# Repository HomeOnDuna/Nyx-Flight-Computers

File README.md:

# Nyx-Flight-Computer
Contains all details of the Nyx family of flight computers developed by Timothy Paige for UNSW rocketry

How to use:
 - Make a local clone of the entire repositry
 - Open the project you want from the file it is in
 - Enjoy!

To add parts to the library:
 - All parts go in the UNSW Rocketry parts folder (single parrts library)
 - Open a project and add the symbol into the UNSW Rocketry Library (symbol library, via import)
 - Put the footprint in the footprints.pretty folder of the parts folder
 - Put the 3D model in the 3D models folder
 - In the project, edit the symbol you have imported and assign the default footprint to the footprints.pretty folder footprint (.kicad_mod)
 - Edit the footprint you just added to add in the 3D model

How to reference filepaths:
**Do not use the default filepaths KiCAD generates. These will only work on your device!**
 - Remove the filepath up to Nyx-Flight-Computers (leave the \ after this)
 - Insert .. before this, which then re-references to a relative filepath (permitting multi-device use).

Current capabilites:
 - Literally nothing

Future capabilities targets:
 - Flight data recording from multiple sources to memory (SD cards)
 - Detection of phase of flight (not vehicle direction, speed etc., only are we 1) accelerating, and 2) going up or going down) and subsequent actions or data recording changes
 - Flight data high-speed capability to RAM during boost phase
 - Telemetry of currently relevant data
 - Pyro / chute deploy devices (linear actuator or other form)
 - Basic marking out of failed / erroring sensors in data recording

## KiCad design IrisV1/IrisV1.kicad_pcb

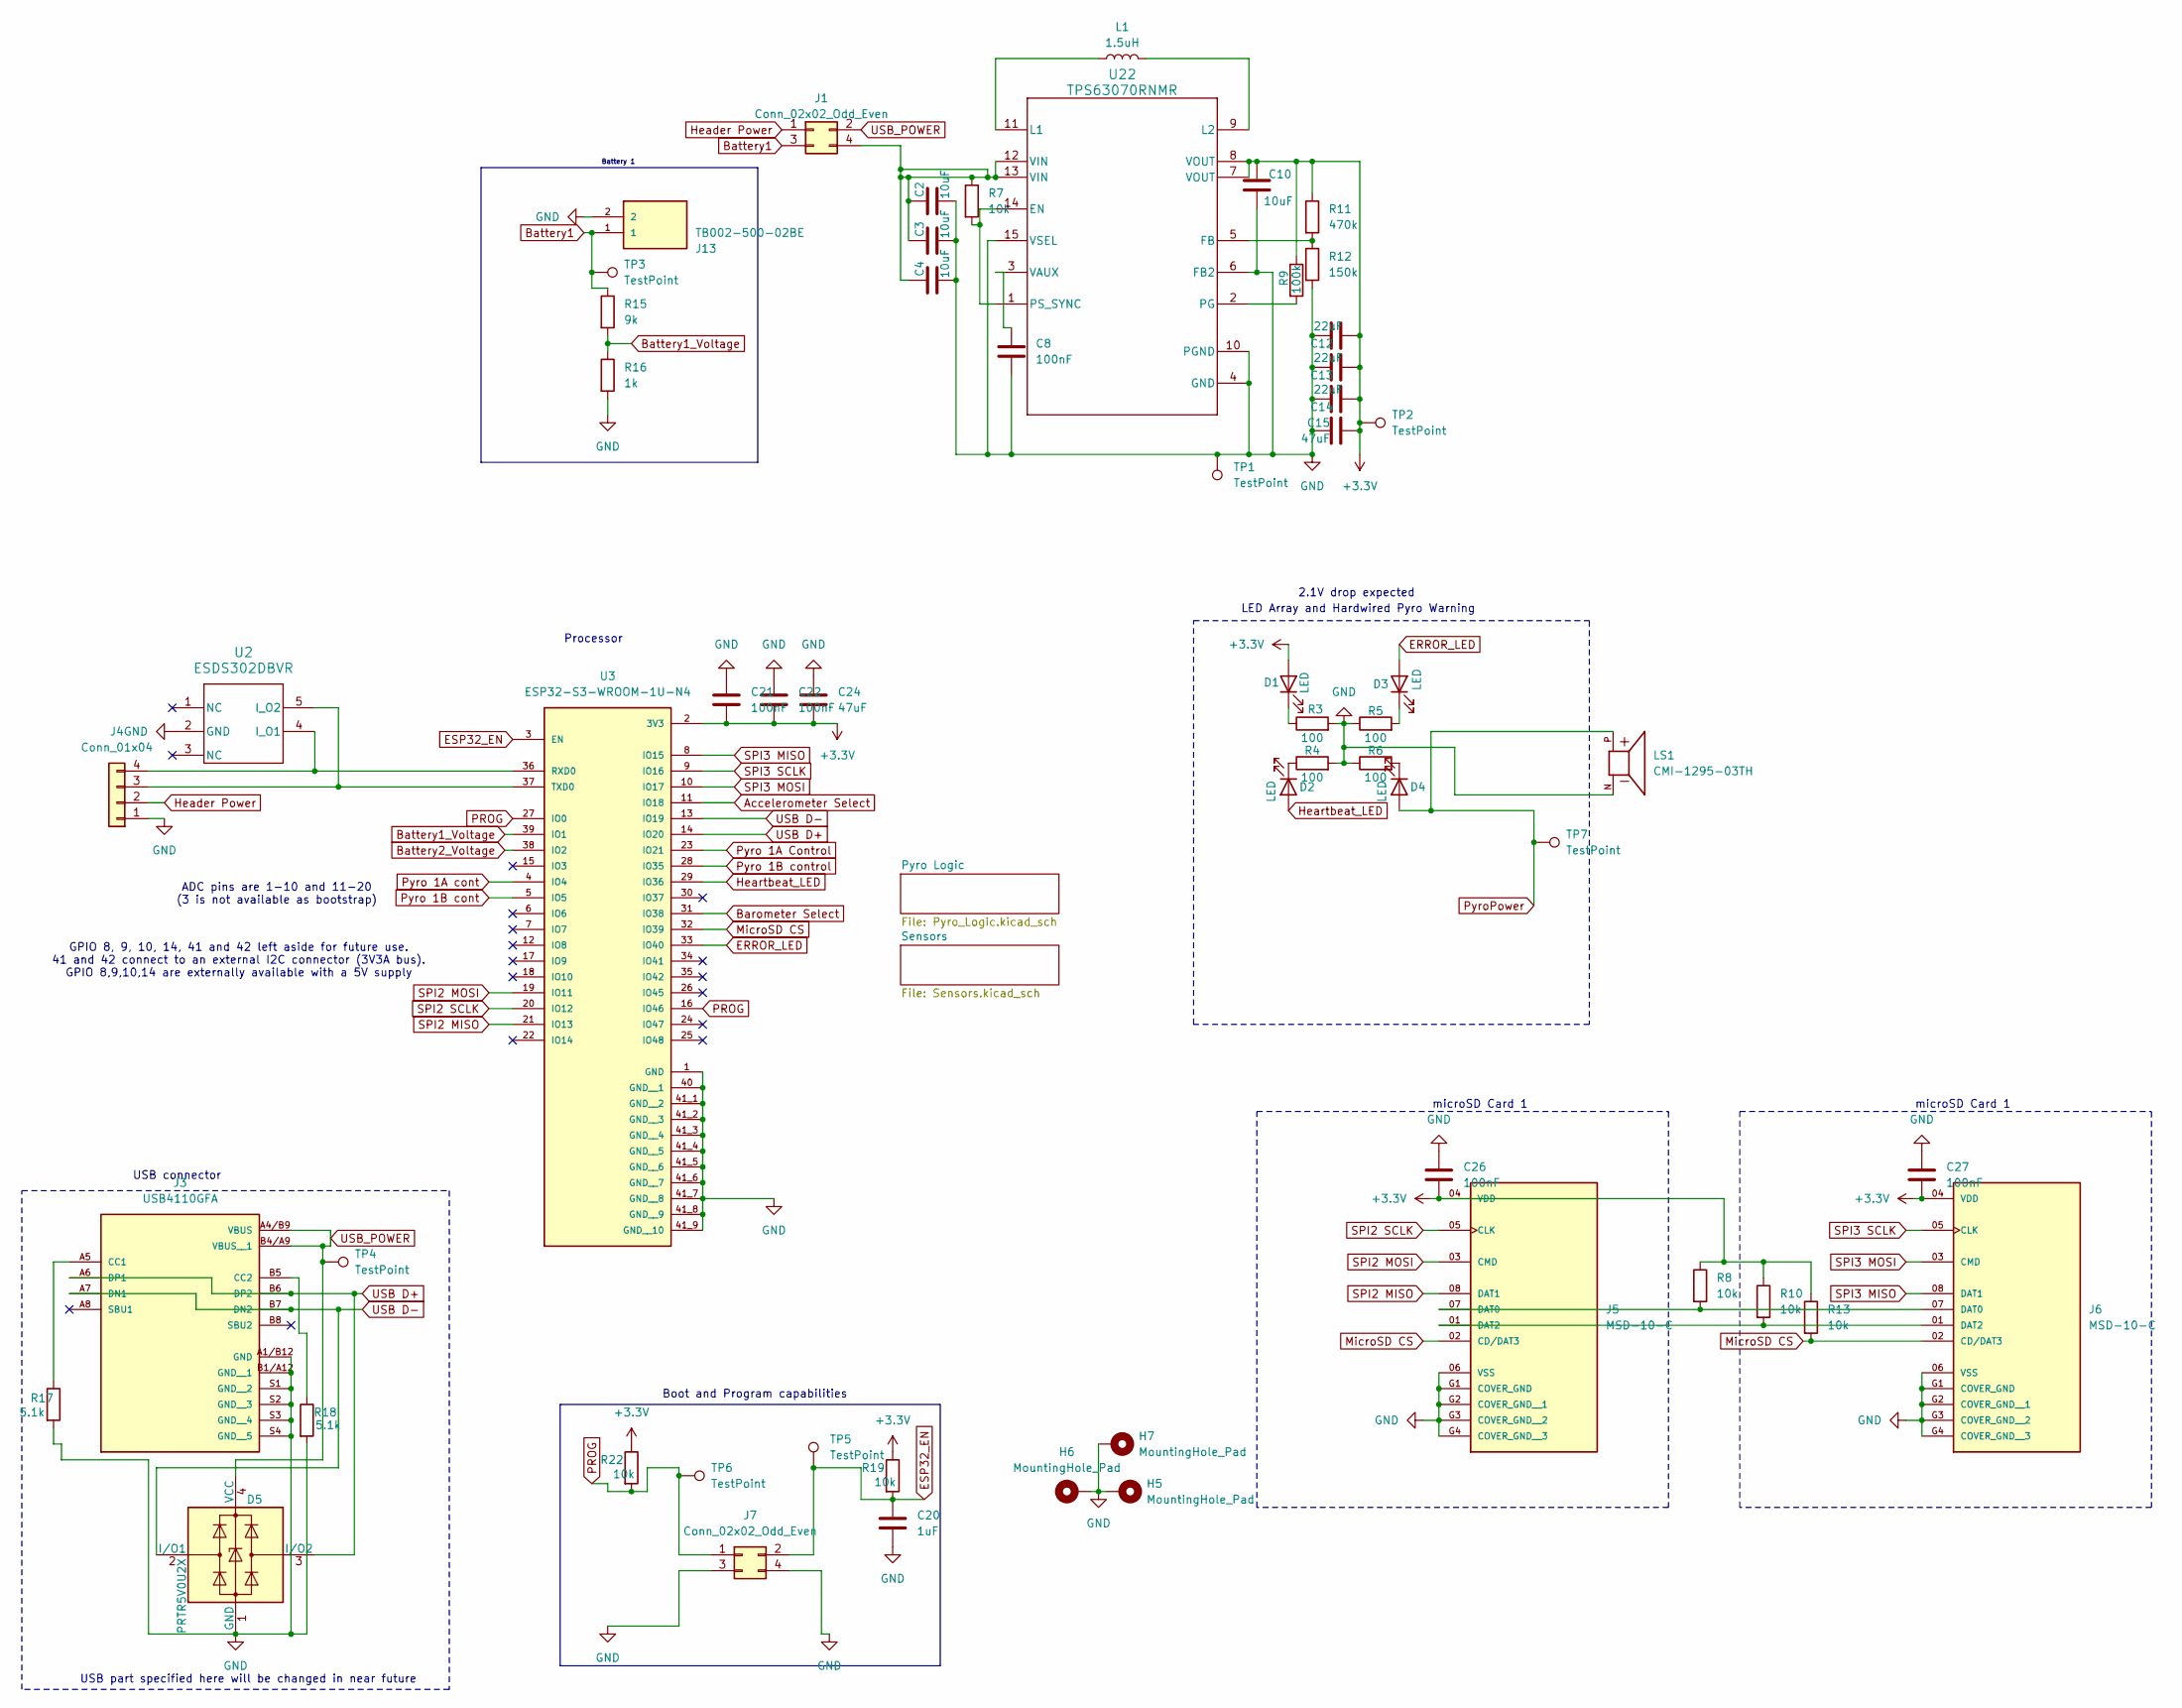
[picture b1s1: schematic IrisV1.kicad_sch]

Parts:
C2, C3, C4, C10: 10uF; C_0603_1608Metric
C8, C21, C22, C26, C27: 100nF; C_0603_1608Metric
C12, C13, C14: 22uF; C_0603_1608Metric
C15, C24: 47uF; C_0603_1608Metric
C20: 1uF; C_0603_1608Metric
D1, D2, D3, D4: LED; LED_0603_1608Metric
D5: PRTR5V0U2X; SOT-143
H5, H6, H7: MountingHole_Pad; MountingHole_3.2mm_M3_ISO7380_Pad_TopBottom
J1, J7: Conn_02x02_Odd_Even; PinHeader_2x02_P2.54mm_Vertical
J3: USB4110GFA; GCT_USB4110GFA
J4: Conn_01x04; PinHeader_1x04_P2.54mm_Vertical
J5, J6: MSD-10-C; CUI_MSD-10-C; PARTREV 1.0
J13: TB002-500-02BE; ADAMTECH_EBWA-02-A; PARTREV A
L1: 1.5uH; 1277AS-H-1R0M=P2_MUR-M
LS1: CMI-1295-03TH; SPKR_CMI-1295-03TH; PARTREV 1.0
R3, R4, R5, R6: 100; R_0603_1608Metric
R7, R8, R10, R13, R19, R22: 10k; R_0603_1608Metric
R9: 100k; R_0603_1608Metric
R11: 470k; R_0603_1608Metric
R12: 150k; R_0603_1608Metric
R15: 9k; R_0603_1608Metric
R16: 1k; R_0603_1608Metric
R17, R18: 5.1k; R_0603_1608Metric
TP1, TP2, TP3, TP4, TP5, TP6, TP7: TestPoint; TestPoint_Pad_D1.5mm
U2: ESDS302DBVR; DBV0005A_N
U3: ESP32-S3-WROOM-1U-N4; XCVR_ESP32-S3-WROOM-1U-N4; PARTREV v1.1
U22: TPS63070RNMR; RNM0015A

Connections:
+3.3V: C10.1, C12.2, C13.2, C14.2, C15.2, C21.2, C22.2, C24.2, C26.2, C27.2, D1.2 (A), J5.04 (VDD), J6.04 (VDD), R8.1, R9.1, R10.1, R11.1, R13.1, R19.1, R22.1, TP2.1 (1_1), U3.2 (3V3), U22.7 (VOUT), U22.8 (VOUT); also elsewhere on the board
Accelerometer Select: U3.11 (IO18); also elsewhere on the board
Barometer Select: U3.31 (IO38); also elsewhere on the board
Battery1: J1.3, J13.1, R15.1, TP3.1 (1_1)
Battery1_Voltage: R15.2, R16.1, U3.39 (IO1)
Battery2_Voltage: U3.38 (IO2); also elsewhere on the board
ERROR_LED: D3.2 (A), U3.33 (IO40)
ESP32_EN: C20.1, J7.2, R19.2, TP5.1 (1_1), U3.3 (EN)
GND: C2.1, C3.1, C4.1, C8.2, C10.2, C12.1, C13.1, C14.1, C15.1, C20.2, C21.1, C22.1, C24.1, C26.1, C27.1, D5.1 (GND), H5.1 (1_1), H6.1 (1_1), H7.1 (1_1), J3.A1/B12 (GND), J3.B1/A12 (GND__1), J3.S1 (GND__2), J3.S2 (GND__3), J3.S3 (GND__4), J3.S4 (GND__5), J4.1, J5.06 (VSS), J5.G1 (COVER_GND), J5.G2 (COVER_GND__1), J5.G3 (COVER_GND__2), J5.G4 (COVER_GND__3), J6.06 (VSS), J6.G1 (COVER_GND), J6.G2 (COVER_GND__1), J6.G3 (COVER_GND__2), J6.G4 (COVER_GND__3), J7.3, J7.4, J13.2, LS1.N, R3.2, R4.2, R5.1, R6.1, R12.2, R16.2, R17.2, R18.2, TP1.1 (1_1), U2.2 (GND), U3.1 (GND), U3.40 (GND__1), U3.41_1 (GND__2), U3.41_2 (GND__3), U3.41_3 (GND__4), U3.41_4 (GND__5), U3.41_5 (GND__6), U3.41_6 (GND__7), U3.41_7 (GND__8), U3.41_8 (GND__9), U3.41_9 (GND__10), U22.4 (GND), U22.6 (FB2), U22.10 (PGND), U22.15 (VSEL); also elsewhere on the board
Header Power: J1.1, J4.2
Heartbeat_LED: D2.2 (A), U3.29 (IO36)
MicroSD CS: J5.02 (CD/DAT3), J6.02 (CD/DAT3), R13.2, U3.32 (IO39)
unnamed: D1.1 (K), R3.1
unnamed: D2.1 (K), R4.1
unnamed: D3.1 (K), R5.2
unnamed: D4.1 (K), R6.2
unnamed: C2.2, C3.2, C4.2, J1.4, R7.1, U22.12 (VIN), U22.13 (VIN)
unnamed: J3.A5 (CC1), R17.1
unnamed: J3.B5 (CC2), R18.1
unnamed: J4.3, U2.5 (I_O2), U3.37 (TXD0)
unnamed: J4.4, U2.4 (I_O1), U3.36 (RXD0)
unnamed: J5.07 (DAT0), J6.07 (DAT0), R8.2
unnamed: J5.01 (DAT2), J6.01 (DAT2), R10.2
unnamed: R7.2, U22.1 (PS_SYNC), U22.14 (EN)
unnamed: R11.2, R12.1, U22.5 (FB)
unnamed: L1.1, U22.11 (L1)
unnamed: L1.2, U22.9 (L2)
unnamed: R9.2, U22.2 (PG)
unnamed: C8.1, U22.3 (VAUX)
PROG: J7.1, R22.2, TP6.1 (1_1), U3.16 (IO46), U3.27 (IO0)
Pyro 1A Control: U3.23 (IO21); also elsewhere on the board
Pyro 1A cont: U3.4 (IO4); also elsewhere on the board
Pyro 1B cont: U3.5 (IO5); also elsewhere on the board
Pyro 1B control: U3.28 (IO35); also elsewhere on the board
PyroPower: D4.2 (A), LS1.P, TP7.1 (1_1); also elsewhere on the board
SPI2 MISO: J5.08 (DAT1), U3.21 (IO13); also elsewhere on the board
SPI2 MOSI: J5.03 (CMD), U3.19 (IO11); also elsewhere on the board
SPI2 SCLK: J5.05 (CLK), U3.20 (IO12); also elsewhere on the board
SPI3 MISO: J6.08 (DAT1), U3.8 (IO15); also elsewhere on the board
SPI3 MOSI: J6.03 (CMD), U3.10 (IO17); also elsewhere on the board
SPI3 SCLK: J6.05 (CLK), U3.9 (IO16); also elsewhere on the board
USB D+: D5.3 (I/O2), J3.A6 (DP1), J3.B6 (DP2), U3.14 (IO20)
USB D-: D5.2 (I/O1), J3.A7 (DN1), J3.B7 (DN2), U3.13 (IO19)
USB_POWER: D5.4 (VCC), J1.2, J3.A4/B9 (VBUS), J3.B4/A9 (VBUS__1), TP4.1 (1_1)

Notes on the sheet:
ADC pins are 1-10 and 11-20 (3 is not available as bootstrap)
2.1V drop expected
Boot and Program capabilities
GPIO 8, 9, 10, 14, 41 and 42 left aside for future use. 41 and 42 connect to an external I2C connector (3V3A bus). GPIO 8,9,10,14 are externally available with a 5V supply
Battery 1
USB part specified here will be changed in near future
Processor
LED Array and Hardwired Pyro Warning
microSD Card 1
USB connector

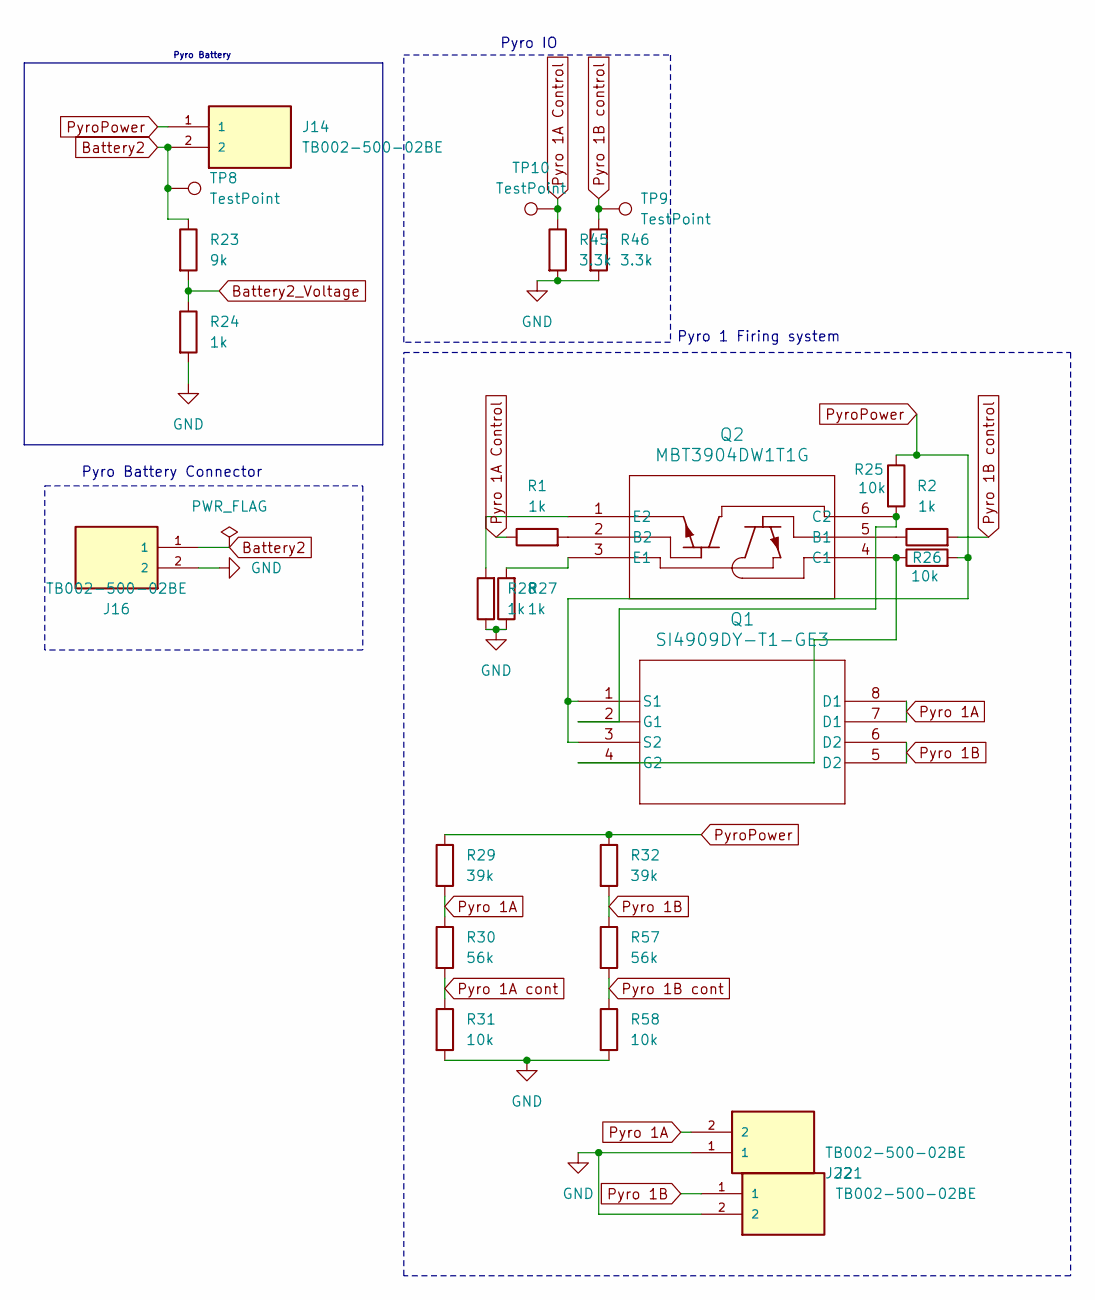
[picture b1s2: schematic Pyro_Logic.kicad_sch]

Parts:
J14, J16, J21, J22: TB002-500-02BE; ADAMTECH_EBWA-02-A; PARTREV A
Q1: SI4909DY-T1-GE3; SOIC_09DY-T1-GE3_VIS
Q2: MBT3904DW1T1G; SOT-363&slash_SC-88&slash_SC70-6&slash_CASE419B_OSI
R1, R2, R24, R27, R28: 1k; R_0603_1608Metric
R23: 9k; R_0603_1608Metric
R25, R26, R31, R58: 10k; R_0603_1608Metric
R29, R32: 39k; R_0603_1608Metric
R30, R57: 56k; R_0603_1608Metric
R45, R46: 3.3k; R_0603_1608Metric
TP8, TP9, TP10: TestPoint; TestPoint_Pad_D1.5mm

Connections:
Battery2: J14.2, J16.1, R23.1, TP8.1 (1_1)
Battery2_Voltage: R23.2, R24.1; also elsewhere on the board
GND: J16.2, J21.2, J22.1, R24.2, R27.1, R28.1, R31.2, R45.2, R46.2, R58.2; also elsewhere on the board
unnamed: Q1.2 (G1), Q2.6 (C2), R25.2
unnamed: Q1.4 (G2), Q2.4 (C1), R26.1
unnamed: Q2.5 (B1), R2.1
unnamed: Q2.2 (B2), R1.2
unnamed: Q2.3 (E1), R27.2
unnamed: Q2.1 (E2), R28.2
Pyro 1A: J22.2, Q1.7 (D1), Q1.8 (D1), R29.2, R30.1
Pyro 1A Control: R1.1, R45.1, TP10.1 (1_1); also elsewhere on the board
Pyro 1A cont: R30.2, R31.1; also elsewhere on the board
Pyro 1B: J21.1, Q1.5 (D2), Q1.6 (D2), R32.2, R57.1
Pyro 1B cont: R57.2, R58.1; also elsewhere on the board
Pyro 1B control: R2.2, R46.1, TP9.1 (1_1); also elsewhere on the board
PyroPower: J14.1, Q1.1 (S1), Q1.3 (S2), R25.1, R26.2, R29.1, R32.1; also elsewhere on the board

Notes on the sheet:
Pyro Battery Connector
Pyro IO
Pyro Battery
Pyro 1 Firing system

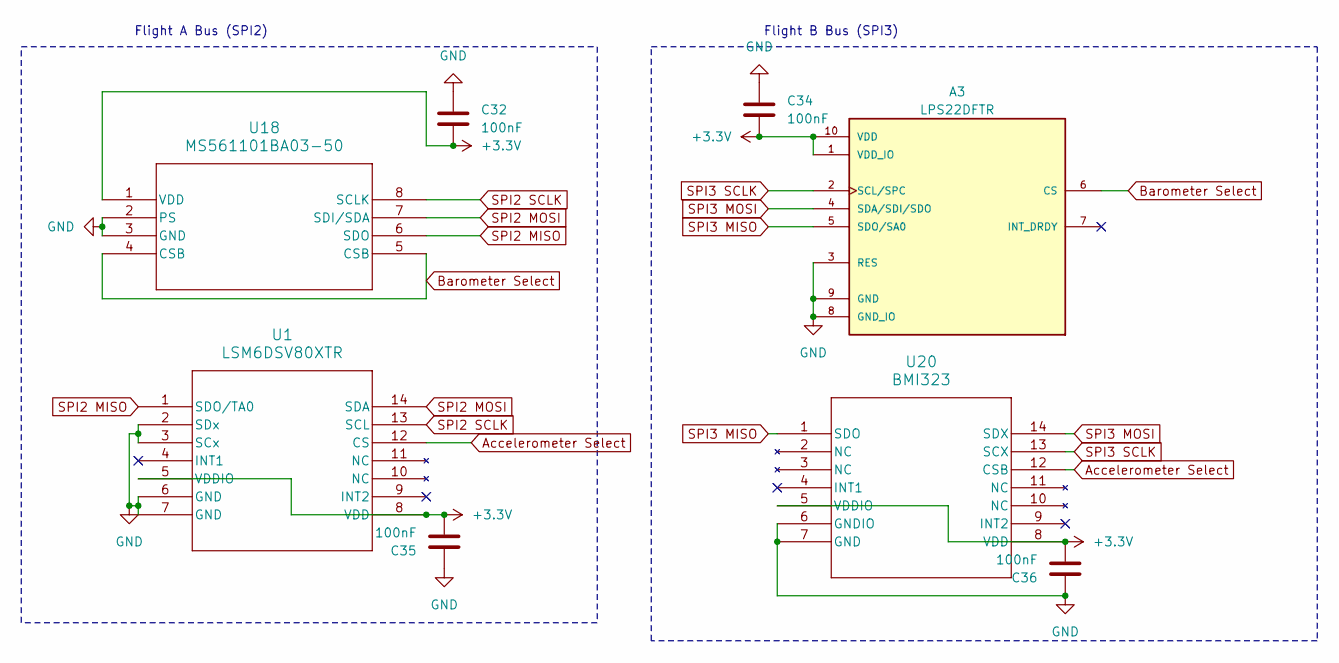
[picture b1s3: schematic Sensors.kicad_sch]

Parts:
A3: LPS22DFTR; XDCR_LPS22DFTR; PARTREV 3
C32, C34, C35, C36: 100nF; C_0603_1608Metric
U1: LSM6DSV80XTR; QFN_LSM6DSV80XTR_STM
U18: MS561101BA03-50; SON8_MS5611_TEC
U20: BMI323; BMI323_BOS

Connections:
+3.3V: A3.1 (VDD_IO), A3.10 (VDD), C32.2, C34.2, C35.2, C36.2, U1.5 (VDDIO), U1.8 (VDD), U18.1 (VDD), U20.5 (VDDIO), U20.8 (VDD); also elsewhere on the board
Accelerometer Select: U1.12 (CS), U20.12 (CSB); also elsewhere on the board
Barometer Select: A3.6 (CS), U18.4 (CSB), U18.5 (CSB); also elsewhere on the board
GND: A3.3 (RES), A3.8 (GND_IO), A3.9 (GND), C32.1, C34.1, C35.1, C36.1, U1.2 (SDx), U1.3 (SCx), U1.6 (GND), U1.7 (GND), U18.2 (PS), U18.3 (GND), U20.6 (GNDIO), U20.7 (GND); also elsewhere on the board
SPI2 MISO: U1.1 (SDO/TA0), U18.6 (SDO); also elsewhere on the board
SPI2 MOSI: U1.14 (SDA), U18.7 (SDI/SDA); also elsewhere on the board
SPI2 SCLK: U1.13 (SCL), U18.8 (SCLK); also elsewhere on the board
SPI3 MISO: A3.5 (SDO/SA0), U20.1 (SDO); also elsewhere on the board
SPI3 MOSI: A3.4 (SDA/SDI/SDO), U20.14 (SDX); also elsewhere on the board
SPI3 SCLK: A3.2 (SCL/SPC), U20.13 (SCX); also elsewhere on the board

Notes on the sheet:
Flight B Bus (SPI3)
Flight A Bus (SPI2)

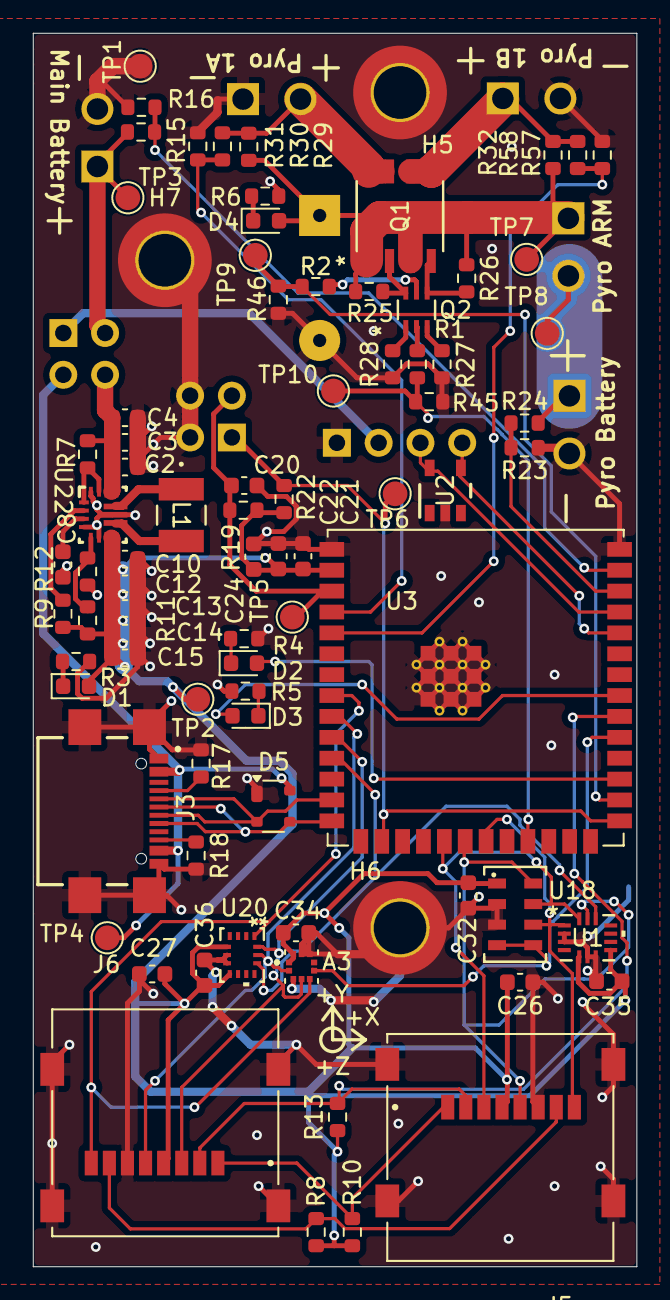
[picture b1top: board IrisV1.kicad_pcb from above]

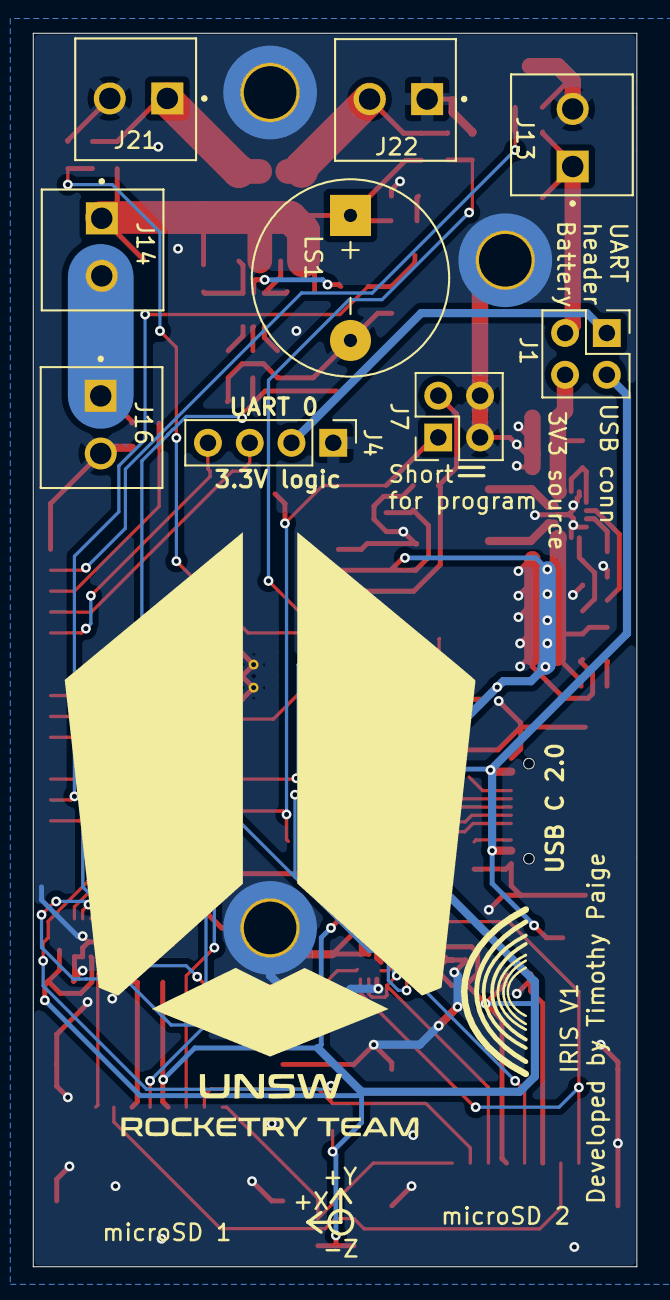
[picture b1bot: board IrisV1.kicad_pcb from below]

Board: 2 copper layers, 36.7 x 75.0 mm, 92 parts (9 on the bottom side), 53 nets.

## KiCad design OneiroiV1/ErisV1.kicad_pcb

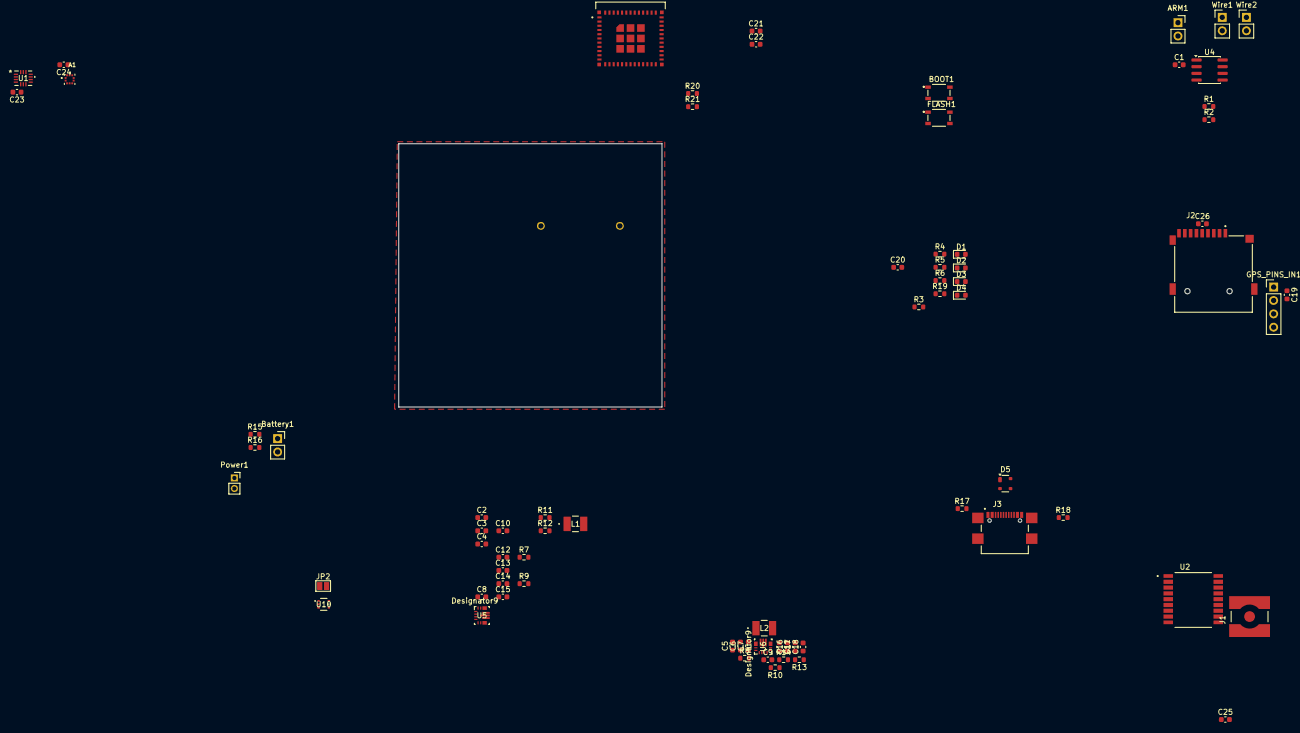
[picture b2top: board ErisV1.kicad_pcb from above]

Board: 4 copper layers, 75 parts (1 on the bottom side), 47 nets, no tracks yet.

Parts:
A1: LPS22DFTR; XDCR_LPS22DFTR
ARM1: SW_SPDT; PinSocket_1x02_P2.54mm_Vertical
BOOT1: SKRPACE010; SW_SKRPACE010
Battery1: Barrel_Jack; PinSocket_1x02_P2.54mm_Vertical
C1, C20: 1uF; C_0603_1608Metric
C2, C3, C4, C5, C6, C7, C10, C11: 10uF; C_0603_1608Metric
C8, C9, C19, C21, C22, C23, C24, C25, C26: 100nF; C_0603_1608Metric
C12, C13, C14, C16, C17, C18: 22uF; C_0603_1608Metric
C15: 47uF; C_0603_1608Metric
D1, D2, D3, D4: LED; LED_0603_1608Metric
D5: PRTR5V0U2X; SOT-143
FLASH1: SKRPACE010; SW_SKRPACE010
GPS_PINS_IN1: Conn_01x04; PinHeader_1x04_P2.54mm_Vertical
J1: CONSMA001-SMD-G-T; LINX_CONSMA001-SMD-G-T
J2: MSD-4-A; CUI_MSD-4-A
J3: USB4110GFA; GCT_USB4110GFA
JP2: SolderJumper_2_Bridged; SolderJumper-2_P1.3mm_Open_Pad1.0x1.5mm
L1, L2: 1.5uH; 1277AS-H-1R0M=P2_MUR-M
LS1: AI-3035-TT-12V-R; XDCR_AI-3035-TT-12V-R
Power1: SW_SPDT; PinSocket_1x02_P2.00mm_Vertical
R1, R2: 3.3k; R_0603_1608Metric
R3, R4, R5: 1.3k; R_0603_1608Metric
R6, R7, R8, R19, R20, R21: 10k; R_0603_1608Metric
R9, R10: 100k; R_0603_1608Metric
R11: 470k; R_0603_1608Metric
R12: 150k; R_0603_1608Metric
R13: 680k; R_0603_1608Metric
R14: 130k; R_0603_1608Metric
R15: 9k; R_0603_1608Metric
R16: 1k; R_0603_1608Metric
R17, R18: 5.1k; R_0603_1608Metric
U1: LSM6DSV80XTR; QFN_LSM6DSV80XTR_STM
U2: MAX-M10S-00B; XCVR_MAX-M10S-00B
U3: ESP32-C6-MINI-1U-N4; XCVR_ESP32-C6-MINI-1U-N4
U4: AO4842_DUAL; SOIC-8_3.9x4.9mm_P1.27mm
U5, U6: TPS63070RNMR; RNM0015A
U10: CVJ10F30_LF; UFV_TOS-L
Wire1, Wire2: Screw_Terminal_01x02; PinHeader_1x02_P2.54mm_Vertical

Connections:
+3.3V: A1.1 (VDD_IO), A1.6 (CS), A1.10 (VDD), C10.1, C12.2, C13.2, C14.2, C15.2, C21.2, C22.2, C23.2, C24.2, C25.2, C26.2, D1.2 (A), J2.4 (VDD), R9.1, R11.1, R19.1, R20.1, R21.1, U1.1 (SDO/TA0), U1.2 (SDx), U1.3 (SCx), U1.5 (VDDIO), U1.8 (VDD), U1.12 (CS), U2.6 (V_BCKP), U2.7 (V_IO), U2.8 (VCC), U3.3 (3V3), U3.20 (IO15), U3.22 (IO8), U5.7 (VOUT), U5.8 (VOUT)
+5V: C11.1, C16.2, C17.2, C18.2, C19.2, D2.2 (A), GPS_PINS_IN1.2, R10.1, R13.1, U6.7 (VOUT), U6.8 (VOUT)
Battery_Voltage: R15.2, R16.1, U3.12 (IO0)
ERROR_LED: D3.2 (A), U3.19 (IO14)
ESP32_EN: BOOT1.1, BOOT1.2, C20.1, R19.2, U3.8 (EN)
GND: A1.3 (RES), A1.5 (SDO/SA0), A1.8 (GND_IO), A1.9 (GND), BOOT1.3, BOOT1.4, Battery1.2, C1.2, C2.1, C3.1, C4.1, C5.1, C6.1, C7.1, C8.2, C9.2, C10.2, C11.2, C12.1, C13.1, C14.1, C15.1, C16.1, C17.1, C18.1, C19.1, C20.2, C21.1, C22.1, C23.1, C24.1, C25.1, C26.1, D5.1 (GND), FLASH1.3, FLASH1.4, GPS_PINS_IN1.1, J1.S1, J1.S2, J2.6 (VSS), J2.G1 (COVER_GND), J2.G2 (COVER_GND__1), J2.G3 (COVER_GND__2), J2.G4 (COVER_GND__3), J3.A1/B12 (GND), J3.B1/A12 (GND__1), J3.S1 (GND__2), J3.S2 (GND__3), J3.S3 (GND__4), J3.S4 (GND__5), LS1.N, R1.2, R2.2, R3.2, R4.2, R5.1, R6.1, R12.2, R14.2, R16.2, R17.2, R18.2, U1.6 (GND), U1.7 (GND), U2.1 (GND), U2.10 (GND__1), U2.12 (GND__2), U3.1 (GND1), U3.2 (GND1__1), U3.11 (GND1__2), U3.14 (GND1__3), U3.36 (GND1__4), U3.37 (GND1__5), U3.38 (GND1__6), U3.39 (GND1__7), U3.40 (GND1__8), U3.41 (GND1__9), U3.42 (GND1__10), U3.43 (GND1__11), U3.44 (GND1__12), U3.45 (GND1__13), U3.46 (GND1__14), U3.47 (GND2), U3.48 (GND2__1), U3.49_1 (GND2__2), U3.49_2 (GND2__3), U3.49_3 (GND2__4), U3.49_4 (GND2__5), U3.49_5 (GND2__6), U3.49_6 (GND2__7), U3.49_7 (GND2__8), U3.49_8 (GND2__9), U3.49_9 (GND2__10), U3.50 (GND2__11), U3.51 (GND2__12), U3.52 (GND2__13), U3.53 (GND2__14), U4.1 (Source1), U4.3 (Source2), U5.4 (GND), U5.6 (FB2), U5.10 (PGND), U5.15 (VSEL), U6.4 (GND), U6.6 (FB2), U6.10 (PGND), U6.15 (VSEL)
GPS_Reset: U2.9 (~RESET), U3.13 (IO1)
I2C0 SCL: A1.2 (SCL/SPC), R20.2, U1.13 (SCL), U2.17 (SCL), U3.25 (IO19)
I2C0 SDA: A1.4 (SDA/SDI/SDO), R21.2, U1.14 (SDA), U2.16 (SDA), U3.24 (IO18)
MAIN_BATTERY: Battery1.1, Power1.2 (B), R15.1
MAIN_POWER: ARM1.2 (B), Power1.1 (A), U10.3 (ANODE_2)
unnamed: D1.1 (K), R3.1
unnamed: D2.1 (K), R4.1
unnamed: D3.1 (K), R5.2
unnamed: D4.1 (K), R6.2
unnamed: J3.A5 (CC1), R17.1
unnamed: J3.B5 (CC2), R18.1
unnamed: JP2.1 (A), U10.4 (CATHODE_2), U10.5 (CATHODE_1)
unnamed: C2.2, C3.2, C4.2, C5.2, C6.2, C7.2, JP2.2 (B), R7.1, R8.1, U5.12 (VIN), U5.13 (VIN), U6.12 (VIN), U6.13 (VIN)
unnamed: J1.1, U2.11 (RF_IN)
unnamed: R7.2, U5.1 (PS_SYNC), U5.14 (EN)
unnamed: R11.2, R12.1, U5.5 (FB)
unnamed: L1.1, U5.11 (L1)
unnamed: L1.2, U5.9 (L2)
unnamed: R9.2, U5.2 (PG)
unnamed: C8.1, U5.3 (VAUX)
unnamed: R8.2, U6.1 (PS_SYNC), U6.14 (EN)
unnamed: R13.2, R14.1, U6.5 (FB)
unnamed: L2.1, U6.11 (L1)
unnamed: L2.2, U6.9 (L2)
unnamed: R10.2, U6.2 (PG)
unnamed: C9.1, U6.3 (VAUX)
PROG: FLASH1.1, FLASH1.2, U3.23 (IO9)
PYRO1: U4.7 (Drain2), U4.8 (Drain2), Wire1.2
PYRO1_control: R1.1, U3.5 (IO2), U4.2 (Gate1)
PYRO2: U4.5 (Drain1), U4.6 (Drain1), Wire2.2
PYRO2_control: R2.1, U3.6 (IO3), U4.4 (Gate2)
PYRO_POWER: ARM1.1 (A), C1.1, D4.2 (A), LS1.P, Wire1.1, Wire2.1
SPI CS: J2.2 (CD/DAT3), U3.26 (IO20)
SPI MISO: J2.7 (DAT0), U3.27 (IO21)
SPI MOSI: J2.3 (CMD), U3.28 (IO22)
SPI SCLK: J2.5 (CLK), U3.29 (IO23)
UART0 RX: GPS_PINS_IN1.3, U3.30 (RXD0)
UART0 TX: GPS_PINS_IN1.4, U3.31 (TXD0)
USB D+: D5.3 (I/O2), J3.A6 (DP1), J3.B6 (DP2), U3.18 (IO13)
USB D-: D5.2 (I/O1), J3.A7 (DN1), J3.B7 (DN2), U3.17 (IO12)
USB_POWER: D5.4 (VCC), J3.A4/B9 (VBUS), J3.B4/A9 (VBUS__1), U10.1 (ANODE_1)

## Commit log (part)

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2026-04-06 Update README.md
    Improved description
2026-05-31 Create test.txt
    Test push
2026-05-31 Push of current state of work
    Moving from local storage of Git Storage
2026-05-31 Standalone
    Making projects standalone
2026-05-31 New Parts library
    Centralising into 1 parts library
2026-05-31 Symbol changes to use common library in Iris
2026-05-31 Iris final update to inbuilt library
2026-05-31 Final set of changes
    Iris is now independent of fixed file systems
2026-05-31 Library update
    Copy across of master library changes
2026-06-01 Using Symlinks in library table instead of folders
    All KiCAD projects now use library tables to refer to the common UNSW Rocketry Parts folder
2026-06-01 Centralised Library
    Updating to a centralised library structure
2026-06-01 Oneiroi Changes
    All 3D models and footprints updated to common library, silkscreening must be re-done.
2026-06-01 Update README.md
    Improved to describe file storage hierarchy
2026-06-01 Silkscreen Oneiroi
    Adds silkscreen to Oneroi
2026-06-03 Small changes
    Swapping final footprints to use relative filepaths for 3D models, silkscreen DRC.
2026-06-08 Changed to 3.5mm Screw terminals
    All screw terminals in IRIS changed to 3.5mm screw terminals per Oliver's request.
2026-06-08 final changes
2026-06-10 Initial Software
    Starting Software development
2026-06-19 Codebase changes
2026-06-24 bom generated
